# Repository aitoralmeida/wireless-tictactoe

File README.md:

wireless-tictactoe
==================

Wireless Tic-Tac-Toe for the THOFU project

Tested with Arduino Mega 2560

Uses https://github.com/joruiz/shiftduino to control the shift registers

 * TicTacToe folder contains the Arduino code
 * PCBSchemas folder contains the Eagle PCB schemas (Square folder contais the schema for each one of the 9 squares)

   This work has been supported by project grant CEN-20101019 (THOFU), funded
by the Spanish Centro para el Desarrollo Tecnol ogico Industrial (CDTI) and
supported by the Spanish Ministerio de Economía y Competitividad.

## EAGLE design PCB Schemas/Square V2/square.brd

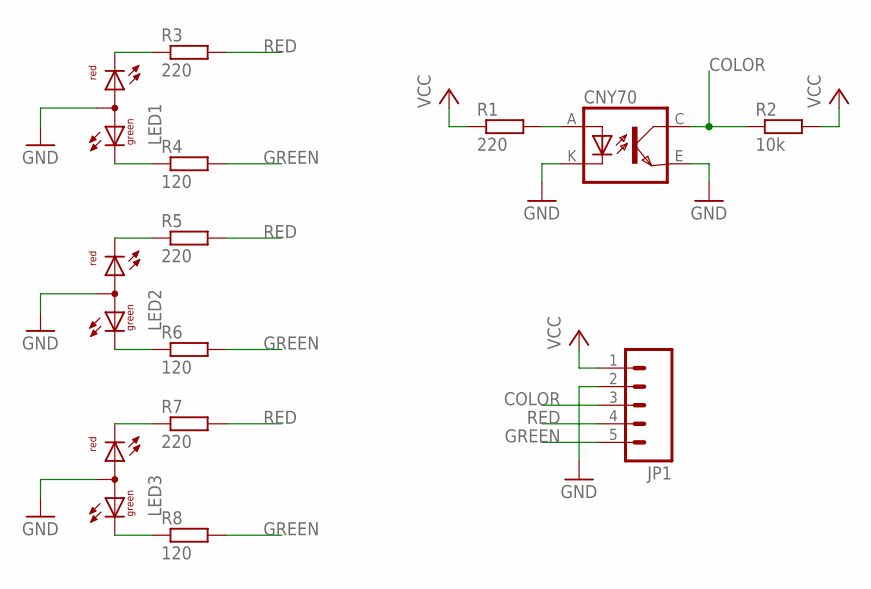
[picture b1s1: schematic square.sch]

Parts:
CNY70: CNY70; 4
JP1: M05PTH; 1X05
LED1, LED2, LED3: L-115WEGW-CA; DUOLED-A-3MM
R1, R3, R5, R7: 220; 0204/7
R2: 10k; 0204/7
R4, R6, R8: 120; 0204/7

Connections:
COLOR: CNY70.C (COL), JP1.3, R2.1
GND: CNY70.E (EMI), CNY70.K (C), JP1.2, LED1.2 (A), LED2.2 (A), LED3.2 (A)
GREEN: JP1.5, R4.2, R6.2, R8.2
unnamed: CNY70.A, R1.2
unnamed: LED1.3 (CR), R3.1
unnamed: LED2.3 (CR), R5.1
unnamed: LED3.3 (CR), R7.1
unnamed: LED2.1 (CG), R6.1
unnamed: LED1.1 (CG), R4.1
unnamed: LED3.1 (CG), R8.1
RED: JP1.4, R3.2, R5.2, R7.2
VCC: JP1.1, R1.1, R2.2

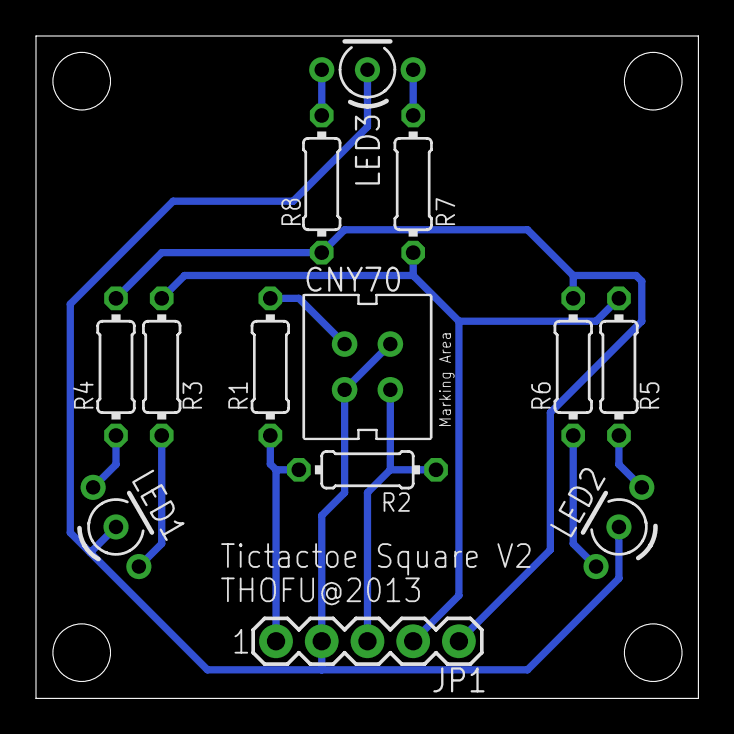
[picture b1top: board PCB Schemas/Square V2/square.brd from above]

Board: 2 copper layers, 36.8 x 36.8 mm, 13 parts (0 on the bottom side), 12 nets.

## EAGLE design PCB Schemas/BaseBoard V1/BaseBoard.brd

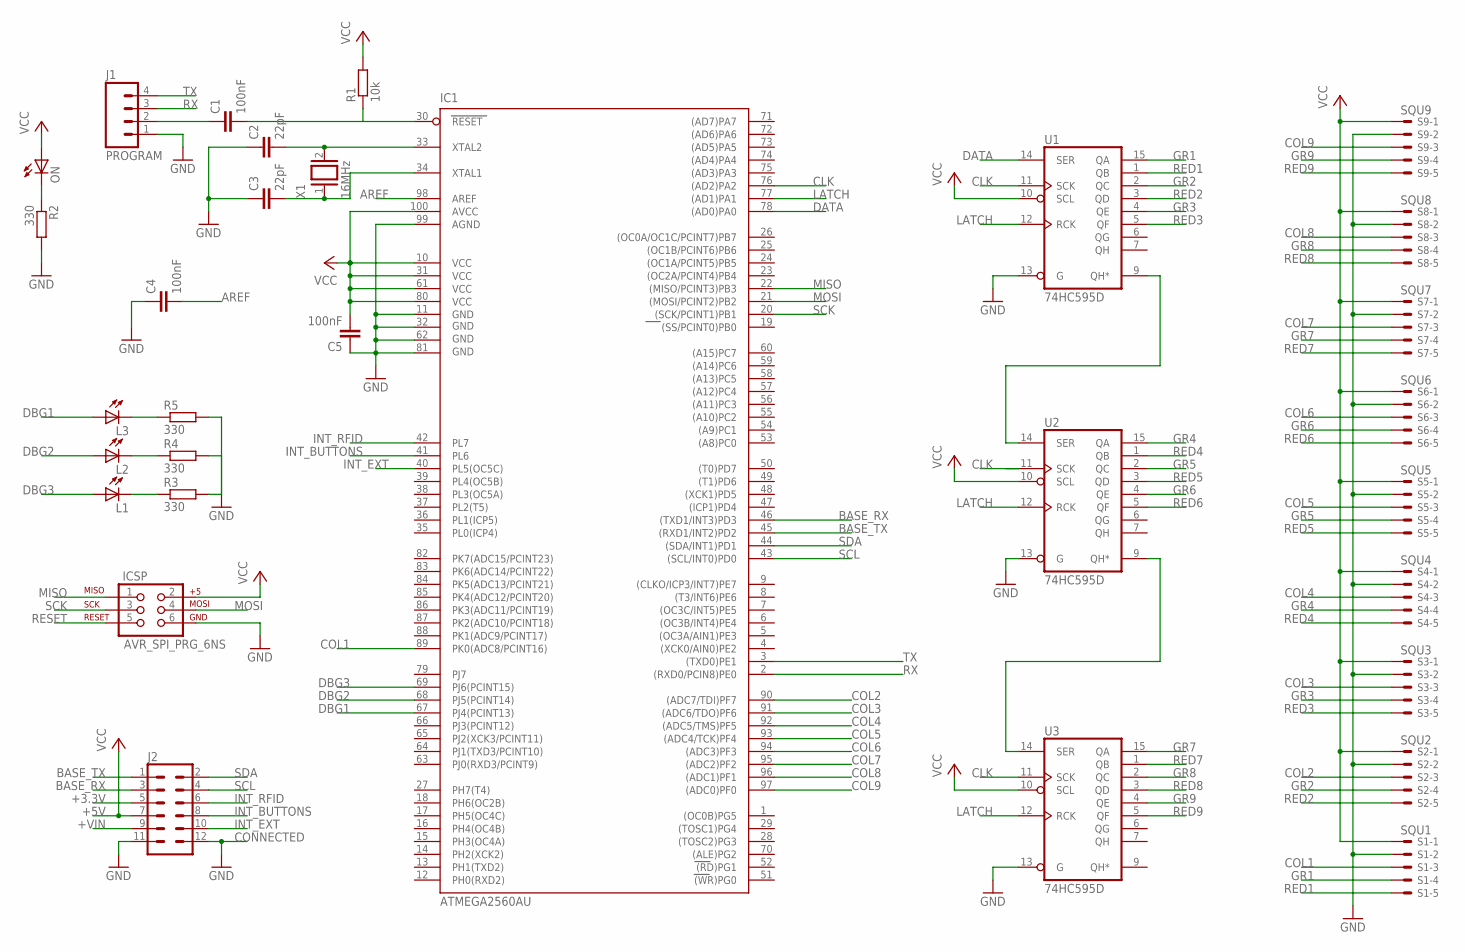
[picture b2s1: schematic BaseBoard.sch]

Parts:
C1, C4, C5: 100nF; C0805
C2, C3: 22pF; C0805
IC1: ATMEGA2560AU; TQFP100
ICSP: AVR_SPI_PRG_6NS; 2X3-NS
J1: PROGRAM; 1X04
J2: CON06X2-2MM; CON06X2_2MM
L1, L2, L3: LEDCHIP-LED0805; CHIP-LED0805
ON: LEDCHIP-LED0805; CHIP-LED0805
R1: 10k; R0805
R2, R3, R4, R5: 330; R0805
S1: SQU1; 53261-05
S2: SQU2; 53261-05
S3: SQU3; 53261-05
S4: SQU4; 53261-05
S5: SQU5; 53261-05
S6: SQU6; 53261-05
S7: SQU7; 53261-05
S8: SQU8; 53261-05
S9: SQU9; 53261-05
U1, U2, U3: 74HC595D; SO16
X1: 16MHz; QS

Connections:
+3.3V: J2.5
+VIN: J2.9
AREF: C4.2, IC1.98 (AREF)
BASE_RX: IC1.46 ((TXD1/INT3)PD3), J2.3
BASE_TX: IC1.45 ((RXD1/INT2)PD2), J2.1
CLK: IC1.76 ((AD2)PA2), U1.11 (SCK), U2.11 (SCK), U3.11 (SCK)
COL1: IC1.89 (PK0(ADC8/PCINT16)), S1.3
COL2: IC1.90 ((ADC7/TDI)PF7), S2.3
COL3: IC1.91 ((ADC6/TDO)PF6), S3.3
COL4: IC1.92 ((ADC5/TMS)PF5), S4.3
COL5: IC1.93 ((ADC4/TCK)PF4), S5.3
COL6: IC1.94 ((ADC3)PF3), S6.3
COL7: IC1.95 ((ADC2)PF2), S7.3
COL8: IC1.96 ((ADC1)PF1), S8.3
COL9: IC1.97 ((ADC0)PF0), S9.3
DATA: IC1.78 ((AD0)PA0), U1.14 (SER)
DBG1: IC1.67 (PJ4(PCINT13)), L3.A
DBG2: IC1.68 (PJ5(PCINT14)), L2.A
DBG3: IC1.69 (PJ6(PCINT15)), L1.A
GND: C2.1, C3.1, C4.1, C5.1, IC1.11 (GND), IC1.32 (GND1), IC1.62 (GND2), IC1.81 (GND3), IC1.99 (AGND), ICSP.6, J1.1, J2.11, J2.12, R2.2, R3.2, R4.2, R5.2, S1.2, S2.2, S3.2, S4.2, S5.2, S6.2, S7.2, S8.2, S9.2, U1.8 (GND), U1.13 (G), U2.8 (GND), U2.13 (G), U3.8 (GND), U3.13 (G)
GR1: S1.4, U1.15 (QA)
GR2: S2.4, U1.2 (QC)
GR3: S3.4, U1.4 (QE)
GR4: S4.4, U2.15 (QA)
GR5: S5.4, U2.2 (QC)
GR6: S6.4, U2.4 (QE)
GR7: S7.4, U3.15 (QA)
GR8: S8.4, U3.2 (QC)
GR9: S9.4, U3.4 (QE)
INT_BUTTONS: IC1.41 (PL6), J2.8
INT_EXT: IC1.40 (PL5(OC5C)), J2.10
INT_RFID: IC1.42 (PL7), J2.6
LATCH: IC1.77 ((AD1)PA1), U1.12 (RCK), U2.12 (RCK), U3.12 (RCK)
MISO: IC1.22 ((MISO/PCINT3)PB3), ICSP.1
MOSI: IC1.21 ((MOSI/PCINT2)PB2), ICSP.4
unnamed: C2.2, IC1.33 (XTAL2), X1.2
unnamed: C3.2, IC1.34 (XTAL1), X1.1
unnamed: L2.C, R4.1
unnamed: L1.C, R3.1
unnamed: C1.1, J1.2
unnamed: U1.9 (QH*), U2.14 (SER)
unnamed: U2.9 (QH*), U3.14 (SER)
unnamed: ON.C, R2.1
unnamed: L3.C, R5.1
RED1: S1.5, U1.1 (QB)
RED2: S2.5, U1.3 (QD)
RED3: S3.5, U1.5 (QF)
RED4: S4.5, U2.1 (QB)
RED5: S5.5, U2.3 (QD)
RED6: S6.5, U2.5 (QF)
RED7: S7.5, U3.1 (QB)
RED8: S8.5, U3.3 (QD)
RED9: S9.5, U3.5 (QF)
RESET: C1.2, IC1.30 (RESET), ICSP.5, R1.1
RX: IC1.2 ((RXD0/PCIN8)PE0), J1.3
SCK: IC1.20 ((SCK/PCINT1)PB1), ICSP.3
SCL: IC1.43 ((SCL/INT0)PD0), J2.4
SDA: IC1.44 ((SDA/INT1)PD1), J2.2
TX: IC1.3 ((TXD0)PE1), J1.4
VCC: C5.2, IC1.10 (VCC), IC1.31 (VCC1), IC1.61 (VCC2), IC1.80 (VCC3), IC1.100 (AVCC), ICSP.2, J2.7, ON.A, R1.2, S1.1, S2.1, S3.1, S4.1, S5.1, S6.1, S7.1, S8.1, S9.1, U1.10 (SCL), U1.16 (VCC), U2.10 (SCL), U2.16 (VCC), U3.10 (SCL), U3.16 (VCC)

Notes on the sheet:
CONNECTED
+5V

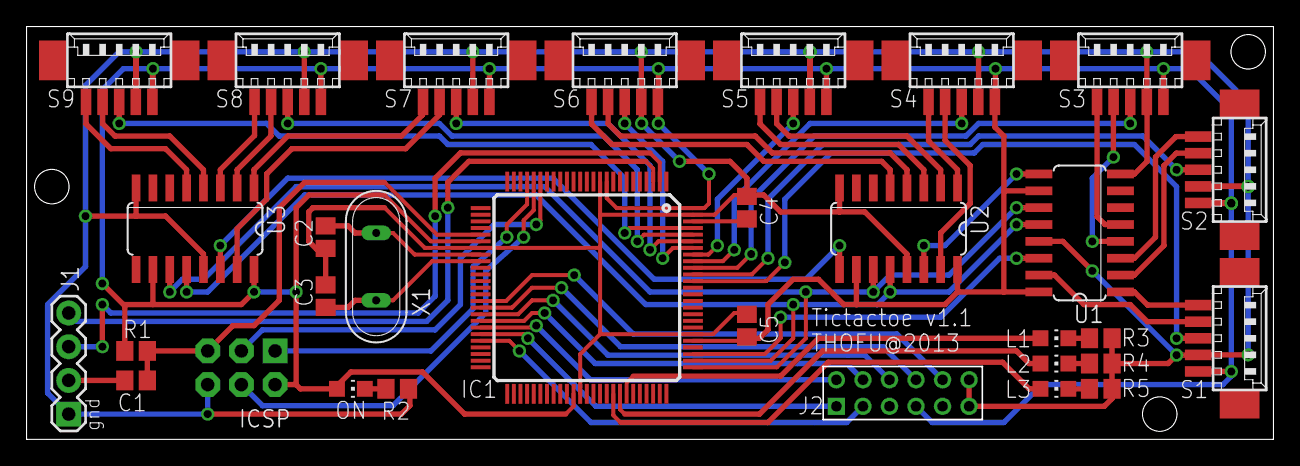
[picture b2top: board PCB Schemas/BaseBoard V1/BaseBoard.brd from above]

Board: 2 copper layers, 93.9 x 31.0 mm, 31 parts (0 on the bottom side), 58 nets.

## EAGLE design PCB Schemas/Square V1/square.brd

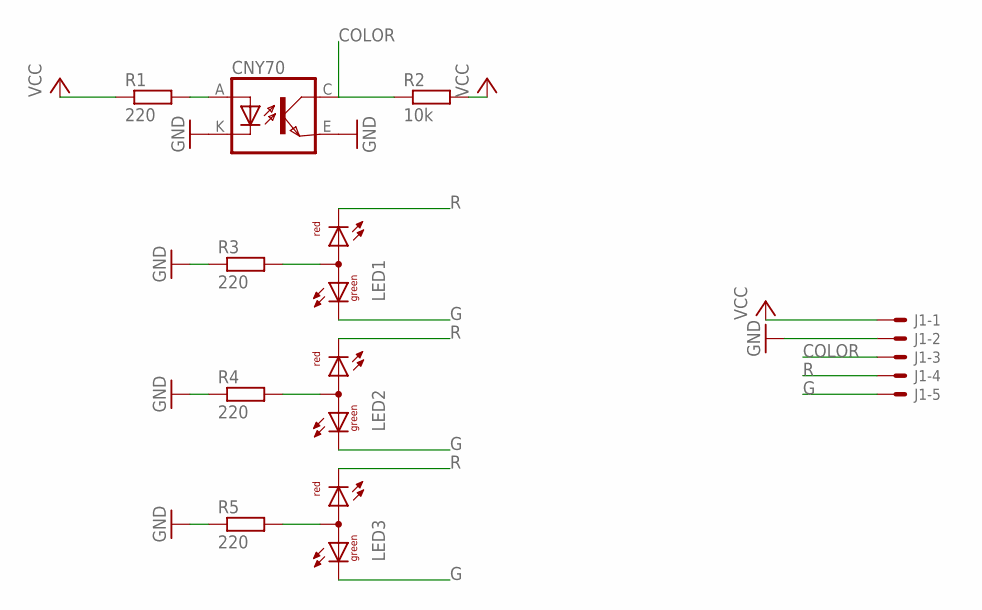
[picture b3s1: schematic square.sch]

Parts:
CNY70: CNY70; 4
J1: CON_5P_1.27
LED1, LED2, LED3: L-115WEGW-CA; DUOLED-A-3MM
R1, R3, R4, R5: 220; 0204/7
R2: 10k; 0204/7

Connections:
COLOR: CNY70.C (COL), J1.3, R2.1; also elsewhere on the board
GND: CNY70.E (EMI), CNY70.K (C), J1.2, R3.1, R4.1, R5.1; also elsewhere on the board
GREEN: J1.5, LED1.1 (CG), LED2.1 (CG), LED3.1 (CG); also elsewhere on the board
unnamed: LED1.2 (A), R3.2
unnamed: CNY70.A, R1.2
unnamed: LED2.2 (A), R4.2
unnamed: LED3.2 (A), R5.2
RED: J1.4, LED1.3 (CR), LED2.3 (CR), LED3.3 (CR); also elsewhere on the board
VCC: J1.1, R1.1, R2.2; also elsewhere on the board

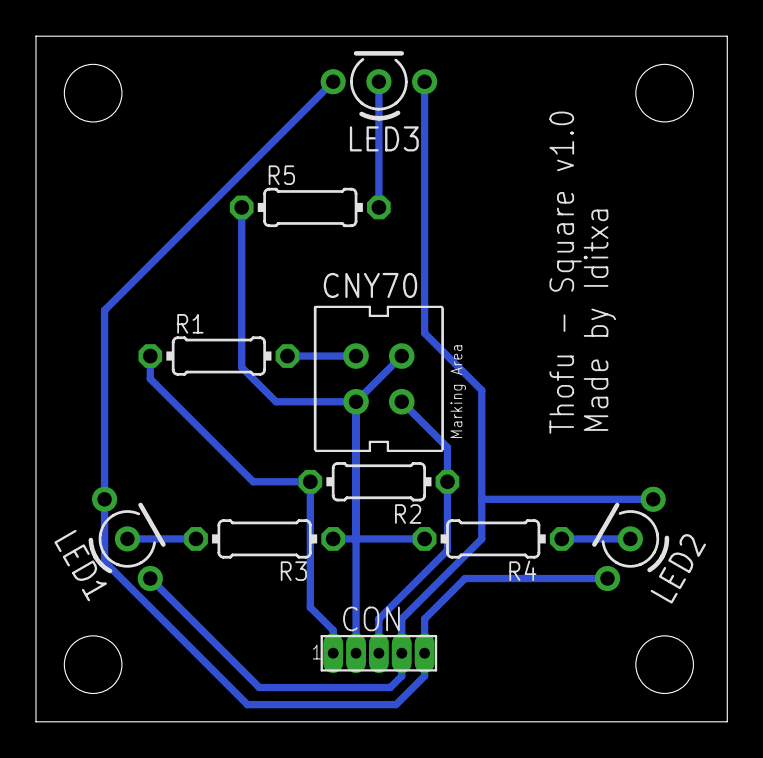
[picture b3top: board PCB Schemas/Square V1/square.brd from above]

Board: 2 copper layers, 38.4 x 38.1 mm, 10 parts (0 on the bottom side), 9 nets.

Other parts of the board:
CON: CON05_2.54MM

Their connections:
COLOR: CON.3; also elsewhere on the board
GND: CON.2; also elsewhere on the board
GREEN: CON.5; also elsewhere on the board
RED: CON.4; also elsewhere on the board
VCC: CON.1; also elsewhere on the board

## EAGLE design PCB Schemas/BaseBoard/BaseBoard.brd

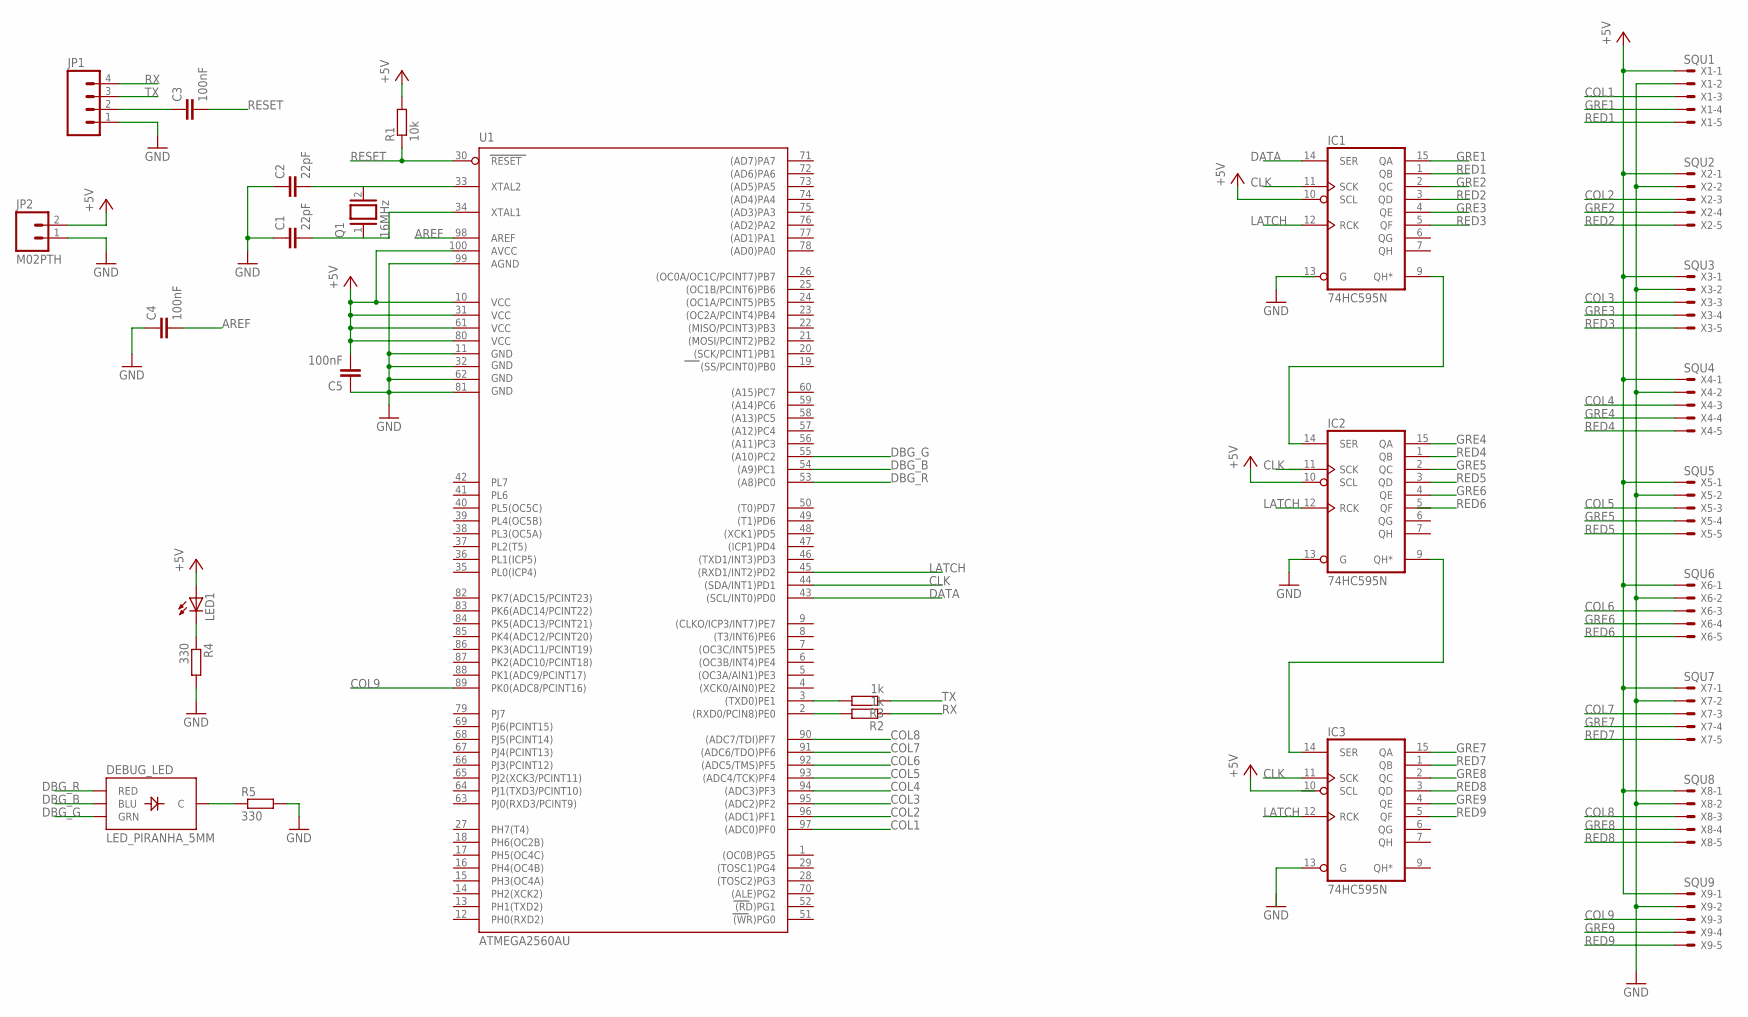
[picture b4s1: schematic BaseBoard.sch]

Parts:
C1, C2: 22pF; C5B2.5
C3, C4, C5: 100nF; C5B3
DEBUG_LED: LED_PIRANHA_5MM
IC1, IC2, IC3: 74HC595N; DIL16
JP1: M04PTH; 1X04
JP2: M02PTH; 1X02
LED1: LED3MM
Q1: 16MHz; QS
R1: 10k; 0204/7
R2, R3: 1k; 0204/7
R4, R5: 330; 0204/7
U1: ATMEGA2560AU; TQFP100
X1: SQU1; 53261-05
X2: SQU2; 53261-05
X3: SQU3; 53261-05
X4: SQU4; 53261-05
X5: SQU5; 53261-05
X6: SQU6; 53261-05
X7: SQU7; 53261-05
X8: SQU8; 53261-05
X9: SQU9; 53261-05

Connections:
AREF: C4.2, U1.98 (AREF)
CLK: IC1.11 (SCK), IC2.11 (SCK), IC3.11 (SCK), U1.44 ((SDA/INT1)PD1)
COL1: U1.97 ((ADC0)PF0), X1.3
COL2: U1.96 ((ADC1)PF1), X2.3
COL3: U1.95 ((ADC2)PF2), X3.3
COL4: U1.94 ((ADC3)PF3), X4.3
COL5: U1.93 ((ADC4/TCK)PF4), X5.3
COL6: U1.92 ((ADC5/TMS)PF5), X6.3
COL7: U1.91 ((ADC6/TDO)PF6), X7.3
COL8: U1.90 ((ADC7/TDI)PF7), X8.3
COL9: U1.89 (PK0(ADC8/PCINT16)), X9.3
DATA: IC1.14 (SER), U1.43 ((SCL/INT0)PD0)
DBG_B: DEBUG_LED.B (BLU), U1.54 ((A9)PC1)
DBG_G: DEBUG_LED.G (GRN), U1.55 ((A10)PC2)
DBG_R: DEBUG_LED.R (RED), U1.53 ((A8)PC0)
GND: C1.1, C2.1, C4.1, C5.1, IC1.8 (GND), IC2.8 (GND), IC2.13 (G), IC3.8 (GND), JP1.1, JP2.1, R4.2, R5.2, U1.11 (GND), U1.32 (GND1), U1.62 (GND2), U1.81 (GND3), U1.99 (AGND), X1.2, X2.2, X3.2, X4.2, X5.2, X6.2, X7.2, X8.2, X9.2
GRE1: IC1.15 (QA), X1.4
GRE2: IC1.2 (QC), X2.4
GRE3: IC1.4 (QE), X3.4
GRE4: IC2.15 (QA), X4.4
GRE5: IC2.2 (QC), X5.4
GRE6: IC2.4 (QE), X6.4
GRE7: IC3.15 (QA), X7.4
GRE8: IC3.2 (QC), X8.4
GRE9: IC3.4 (QE), X9.4
LATCH: IC1.12 (RCK), IC2.12 (RCK), IC3.12 (RCK), U1.45 ((RXD1/INT2)PD2)
unnamed: C2.2, Q1.2, U1.33 (XTAL2)
unnamed: C1.2, U1.34 (XTAL1)
unnamed: R3.2, U1.3 ((TXD0)PE1)
unnamed: R2.2, U1.2 ((RXD0/PCIN8)PE0)
unnamed: C3.1, JP1.2
unnamed: IC1.9 (QH*), IC2.14 (SER)
unnamed: IC2.9 (QH*), IC3.14 (SER)
unnamed: LED1.K (C), R4.1
unnamed: DEBUG_LED.- (C), R5.1
RED1: IC1.1 (QB), X1.5
RED2: IC1.3 (QD), X2.5
RED3: IC1.5 (QF), X3.5
RED4: IC2.1 (QB), X4.5
RED5: IC2.3 (QD), X5.5
RED6: X6.5
RED7: IC3.1 (QB), X7.5
RED8: IC3.3 (QD), X8.5
RED9: IC3.5 (QF), X9.5
RESET: C3.2, R1.1, U1.30 (RESET)
RX: JP1.4, R2.1
TX: JP1.3, R3.1
VCC: C5.2, IC1.10 (SCL), IC1.16 (VCC), IC2.10 (SCL), IC2.16 (VCC), IC3.16 (VCC), JP2.2, LED1.A, R1.2, U1.10 (VCC), U1.31 (VCC1), U1.61 (VCC2), U1.80 (VCC3), U1.100 (AVCC), X1.1, X2.1, X3.1, X4.1, X5.1, X6.1, X7.1, X8.1, X9.1

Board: 2 copper layers, 28 parts (0 on the bottom side), 47 nets, no tracks yet.

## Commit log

2013-05-09 tests for the bi-color leds and the CNY70
2013-05-09 Main program of the tictactoe
2013-05-09 library to control the 74HC595 multiplexor (see http://bildr.org/?s=74hc595)
2013-05-10 moved libraries to libs/Shift/
2013-05-10 test using the 7HC595 shift registers
2013-05-10 added 74HC95
2013-05-10 added support for 2 shift registers
2013-05-10 now controling 3 leds with 2 chainned shif registers
2013-05-16 reorganized the project
2013-05-16 minor change
2013-05-24 Updated and Finalized Square Board V1
2013-05-30 Revised square board V1 and added components file
2013-09-19 adde
2013-09-19 added test for the shift register
2013-09-19 completed the schema, still need to add the comm bus
2013-09-19 changed the test for the squares
2013-09-19 board still needs some work
2013-09-20 changed schema and board
2013-09-26 added first code to check the status of the board
2013-09-26 added some game status control
2013-09-27 some minor changes
2013-09-30 added cny7' values for painted chips (using acrylic paint)
2013-09-30 Square Version 1 finalized
2013-10-24 Finalized base board and square v2
2013-11-13 Corrected BaseBoard V1 and updated license file
2013-11-16 Modified base conector; delete reset pin
2013-11-17 Update base conector package
2013-11-22 Updated details
2013-11-22 Changed debug pins
2013-11-22 Revert "Changed debug pins"
    This reverts commit 73787cc4df0c0002b7e389e6993c433356a097db.
2013-11-22 Added debug led test program and new pins_arduino.h directive file
2013-11-26 added test for all the leds and the cny70s
2013-11-26 added victory loop
2013-12-05 Finalized V2 of base board
2013-12-12 Created class to control each square
2013-12-13 fixed bug calculating the led pins
2013-12-13 fixed bug with private properties
2013-12-13 Added methods to get green and red pins. Renamed the method to calculate them
2013-12-13 fixed bug calculating pins, now it should be working (for real this time)
2013-12-13 added method to recover the color float value
2013-12-13 Implemented calibration and color adjust
2013-12-16 Added victory detection
2013-12-16 Added method for restarting the game
2013-12-16 changed how update color status works. Now it allows to take back pieces
2013-12-16 minor change in the victory loop
2014-01-08 added checkColor method for calibration purposes
2014-06-06 Revised PCB schemas
2014-07-03 added methods to initialize the baseboard screen and rfid reader. Added welcome msg. Better documentation.
2014-07-03 added player turn logic
2014-07-03 added rival turn logic
2014-07-03 added logic to restart the game after victory
2014-07-04 the server randomly selects which player has the first move
2014-07-04 added sound
2014-07-04 tweaked a bit the welcome msg
2014-07-04 moved the sound addresses to the define block
2014-07-04 fixed minor bug in isSame()
2014-07-07 Initial version of the tictactoe server. The registration process is already implemented.
2014-07-07 first version of the game loop, not tested yet
2014-07-08 tested the simple game loop
2014-07-08 added turn control
2014-07-08 changed some of the log msgs
2014-07-09 added communication methods
2014-07-09 added register command
2014-07-09 added findPlayer command
2014-07-09 added do_move command
2014-07-09 added get_move command
2014-07-09 minor bug (toInt)
2014-07-10 Changed a bit how the rivals move is retrieved
2014-07-14 changed sound files numeration
2014-07-14 connections aren't closed by the server now
2014-07-15 changed sep_char to ','
2014-07-15 changed protocol, now there are command and parameter separatos
2014-07-15 changed the protocol in the arduino side also
2014-07-16 added images
2014-07-16 modified the nono file address
2014-07-22 added the board initialization commands, still needs work
2014-07-22 added board initialization and communication methods
2014-07-22 added more log msgs
2014-07-22 added more logging msgs. Fixed bug when identifiying the commands.
2014-07-22 fixed turn identification bug
2014-07-22 new sensor calibration
2014-07-22 fixed bug in sendMove()
2014-07-22 fixed bug sending move
2014-07-23 fixed bug in sendAndWait()
2014-07-23 fixed the bug introduced in initializeBoard in the previous commit
2014-07-23 changed the turn assigment char
2014-07-23 fixed bug: turn+1
2014-07-23 fixed getMove bug in server
2014-07-24 fixed bug in isSame()
2014-07-24 Moved some msgs and command to consts. The previous version works correctly
2014-07-24 removed some todos
2014-09-05 added define for player id.
2014-09-08 new color calibration
2014-09-10 changed the victory loop. Now it does not include the restart option (it wasn't working properly)

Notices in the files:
parts and their libraries:
SparkFun-DigitalIC: Licensing: CC v3.0 Share-Alike You are welcome to use this library for commercial purposes.
